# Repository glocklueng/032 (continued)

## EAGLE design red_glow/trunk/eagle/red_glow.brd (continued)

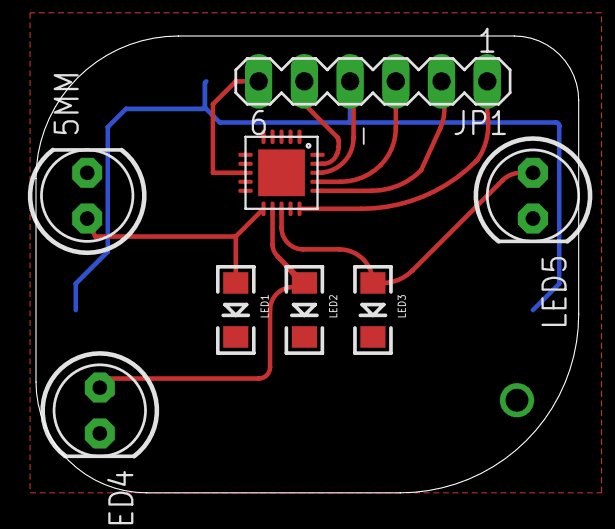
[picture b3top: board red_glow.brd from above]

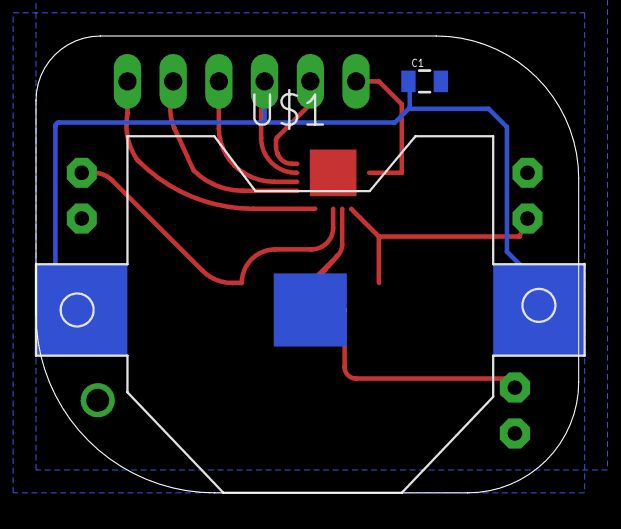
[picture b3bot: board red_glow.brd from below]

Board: 2 copper layers, 30.2 x 25.4 mm, 10 parts (2 on the bottom side), 9 nets.

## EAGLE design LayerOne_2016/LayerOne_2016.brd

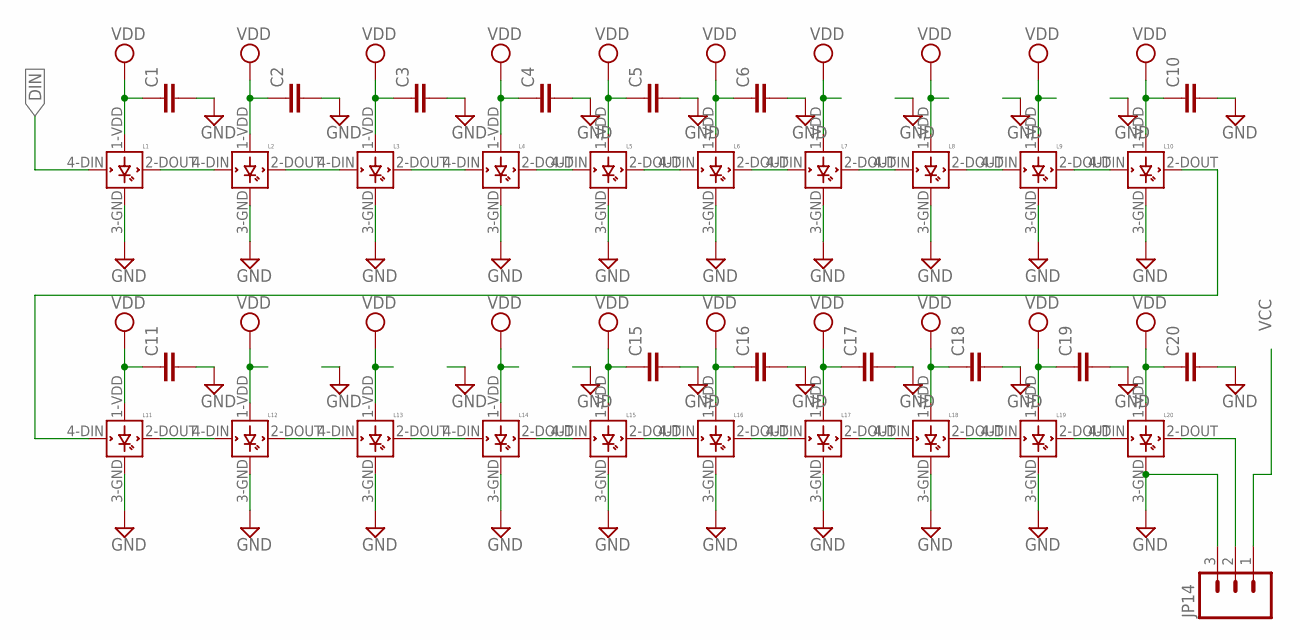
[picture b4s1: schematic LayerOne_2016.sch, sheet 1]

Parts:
C1, C2, C3, C4, C5, C6, C10, C11, C15, C16, C17, C18, C19, C20: CAP0805; 0805
JP14: M031X03_NO_SILK; 1X03_NO_SILK
L1, L2, L3, L4, L5, L6, L7, L8, L9, L10, L11, L12, L13, L14, L15, L16, L17, L18, L19, L20: WS2812B

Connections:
DIN: L1.4-DIN (DIN); also elsewhere on the board
GND: C1.2, C2.2, C3.2, C4.2, C5.2, C6.2, C10.2, C11.2, C15.2, C16.2, C17.2, C18.2, C19.2, C20.2, JP14.3, L1.3-GND (GND), L2.3-GND (GND), L3.3-GND (GND), L4.3-GND (GND), L5.3-GND (GND), L6.3-GND (GND), L7.3-GND (GND), L8.3-GND (GND), L9.3-GND (GND), L10.3-GND (GND), L11.3-GND (GND), L12.3-GND (GND), L13.3-GND (GND), L14.3-GND (GND), L15.3-GND (GND), L16.3-GND (GND), L17.3-GND (GND), L18.3-GND (GND), L19.3-GND (GND), L20.3-GND (GND); also elsewhere on the board
unnamed: L1.2-DOUT (DOUT), L2.4-DIN (DIN)
unnamed: L3.2-DOUT (DOUT), L4.4-DIN (DIN)
unnamed: L4.2-DOUT (DOUT), L5.4-DIN (DIN)
unnamed: L5.2-DOUT (DOUT), L6.4-DIN (DIN)
unnamed: L6.2-DOUT (DOUT), L7.4-DIN (DIN)
unnamed: L7.2-DOUT (DOUT), L8.4-DIN (DIN)
unnamed: L8.2-DOUT (DOUT), L9.4-DIN (DIN)
unnamed: L9.2-DOUT (DOUT), L10.4-DIN (DIN)
unnamed: L11.2-DOUT (DOUT), L12.4-DIN (DIN)
unnamed: L12.2-DOUT (DOUT), L13.4-DIN (DIN)
unnamed: L13.2-DOUT (DOUT), L14.4-DIN (DIN)
unnamed: L14.2-DOUT (DOUT), L15.4-DIN (DIN)
unnamed: L15.2-DOUT (DOUT), L16.4-DIN (DIN)
unnamed: L16.2-DOUT (DOUT), L17.4-DIN (DIN)
unnamed: L17.2-DOUT (DOUT), L18.4-DIN (DIN)
unnamed: L18.2-DOUT (DOUT), L19.4-DIN (DIN)
unnamed: L19.2-DOUT (DOUT), L20.4-DIN (DIN)
unnamed: L10.2-DOUT (DOUT), L11.4-DIN (DIN)
unnamed: JP14.2, L20.2-DOUT (DOUT)
unnamed: L2.2-DOUT (DOUT), L3.4-DIN (DIN)
VCC: C1.1, C2.1, C3.1, C4.1, C5.1, C6.1, C10.1, C11.1, C15.1, C16.1, C17.1, C18.1, C19.1, C20.1, JP14.1, L1.1-VDD (VDD), L2.1-VDD (VDD), L3.1-VDD (VDD), L4.1-VDD (VDD), L5.1-VDD (VDD), L6.1-VDD (VDD), L7.1-VDD (VDD), L8.1-VDD (VDD), L9.1-VDD (VDD), L10.1-VDD (VDD), L11.1-VDD (VDD), L12.1-VDD (VDD), L13.1-VDD (VDD), L14.1-VDD (VDD), L15.1-VDD (VDD), L16.1-VDD (VDD), L17.1-VDD (VDD), L18.1-VDD (VDD), L19.1-VDD (VDD), L20.1-VDD (VDD); also elsewhere on the board

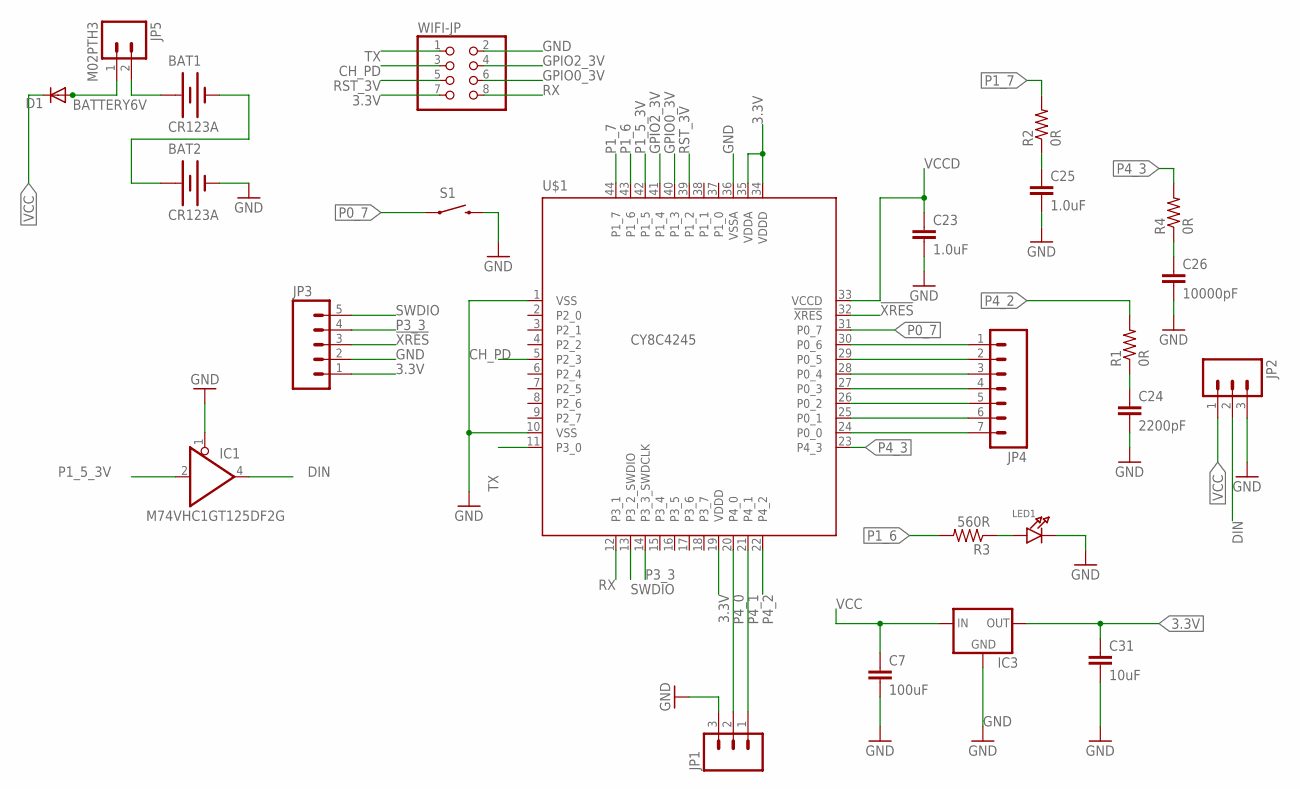
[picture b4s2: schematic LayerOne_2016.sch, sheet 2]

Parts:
BAT1, BAT2: CR123A; TVBGONE-ADJ_BATTERY_CR123A
C7: 100uF; 0805
C23, C25: 1.0uF; 0805
C24: 2200pF; 0805
C26: 10000pF; 0805
C31: 10uF; 0805
D1: DIODESMA; SMA-DIODE
IC1: M74VHC1GT125DF2G; SOT23-5; PARTNO M74VHC1GT125DF2G; DIGIKEY-ND M74VHC1GT125DF1GOSCT-ND
IC3: LM1117; SOT223
JP1, JP2: M031X03_NO_SILK; 1X03_NO_SILK
JP3: M05PTH; 1X05
JP4: M07; 1X07
JP5: M02PTH3; 1X02_LONGPADS
LED1: LED0805; CHIPLED_0805
R1, R2, R4: 0R; 0805
R3: 560R; 0805
S1: SPARKFUN_SWITCH-MOMENTARY-2SMD; SPARKFUN_TACTILE_SWITCH_SMD
U$1: CY8C4245; TQFP44
WIFI-JP: PINHD-2X4; 2X04

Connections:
3.3V: C31.1, IC3.2 (OUT), JP3.1, U$1.19 (VDDD), U$1.34 (VDDD), U$1.35 (VDDA), WIFI-JP.7; also elsewhere on the board
!XRES: JP3.3, U$1.32 (!XRES)
BATTERY6V: D1.A, JP5.1
CH_PD: U$1.5 (P2_3), WIFI-JP.3
DIN: IC1.4 (O), JP2.2; also elsewhere on the board
GND: BAT2.-, C7.2, C23.2, C24.2, C25.2, C26.2, C31.2, IC1.1 (OE), IC1.3 (GND), IC3.1 (GND), JP1.3, JP2.3, JP3.2, LED1.C, S1.3 (2), U$1.1 (VSS), U$1.10 (VSS), U$1.36 (VSSA), WIFI-JP.2; also elsewhere on the board
GPIO0_3V: U$1.40 (P1_3), WIFI-JP.6
GPIO2_3V: U$1.41 (P1_4), WIFI-JP.4
unnamed: C24.1, R1.1
unnamed: C25.1, R2.1
unnamed: C26.1, R4.1
unnamed: LED1.A, R3.1
unnamed: BAT1.-, BAT2.+
unnamed: JP4.7, U$1.24 (P0_0)
unnamed: JP4.6, U$1.25 (P0_1)
unnamed: JP4.5, U$1.26 (P0_2)
unnamed: JP4.4, U$1.27 (P0_3)
unnamed: JP4.3, U$1.28 (P0_4)
unnamed: JP4.2, U$1.29 (P0_5)
unnamed: JP4.1, U$1.30 (P0_6)
unnamed: BAT1.+, JP5.2
P0_7: S1.1, U$1.31 (P0_7)
P1_5_3V: IC1.2 (I), U$1.42 (P1_5)
P1_6: R3.2, U$1.43 (P1_6)
P1_7: R2.2, U$1.44 (P1_7)
P3_3: JP3.4, U$1.14 (P3_3_SWDCLK)
P4_0: JP1.2, U$1.20 (P4_0)
P4_1: JP1.1, U$1.21 (P4_1)
P4_2: R1.2, U$1.22 (P4_2)
P4_3: R4.2, U$1.23 (P4_3)
RST_3V: U$1.39 (P1_2), WIFI-JP.5
RX: U$1.12 (P3_1), WIFI-JP.8
SWDIO: JP3.5, U$1.13 (P3_2_SWDIO)
TX: U$1.11 (P3_0), WIFI-JP.1
VCC: C7.1, D1.C, IC1.5 (VCC), IC3.3 (IN), JP2.1; also elsewhere on the board
VCCD: C23.1, U$1.33 (VCCD)

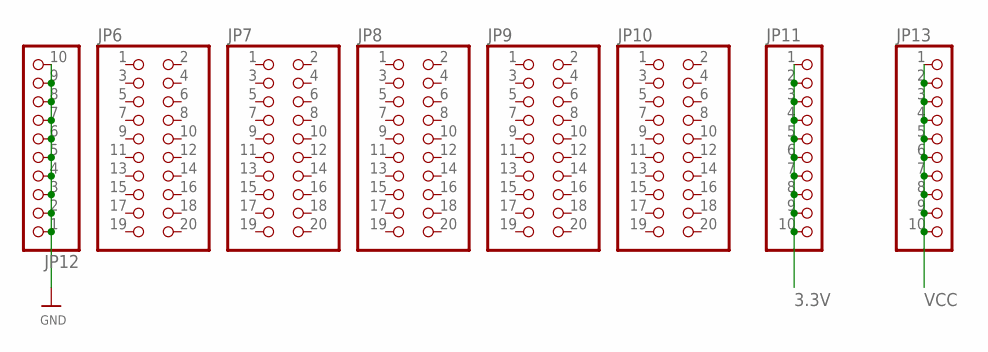
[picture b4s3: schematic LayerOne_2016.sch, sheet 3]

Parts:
JP6, JP7, JP8, JP9, JP10: PINHD-2X10; 2X10
JP11, JP12, JP13: HEADER-1X10; 1X10_OVAL

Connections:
3.3V: JP11.1, JP11.2, JP11.3, JP11.4, JP11.5, JP11.6, JP11.7, JP11.8, JP11.9, JP11.10; also elsewhere on the board
GND: JP12.1, JP12.2, JP12.3, JP12.4, JP12.5, JP12.6, JP12.7, JP12.8, JP12.9, JP12.10; also elsewhere on the board
VCC: JP13.1, JP13.2, JP13.3, JP13.4, JP13.5, JP13.6, JP13.7, JP13.8, JP13.9, JP13.10; also elsewhere on the board

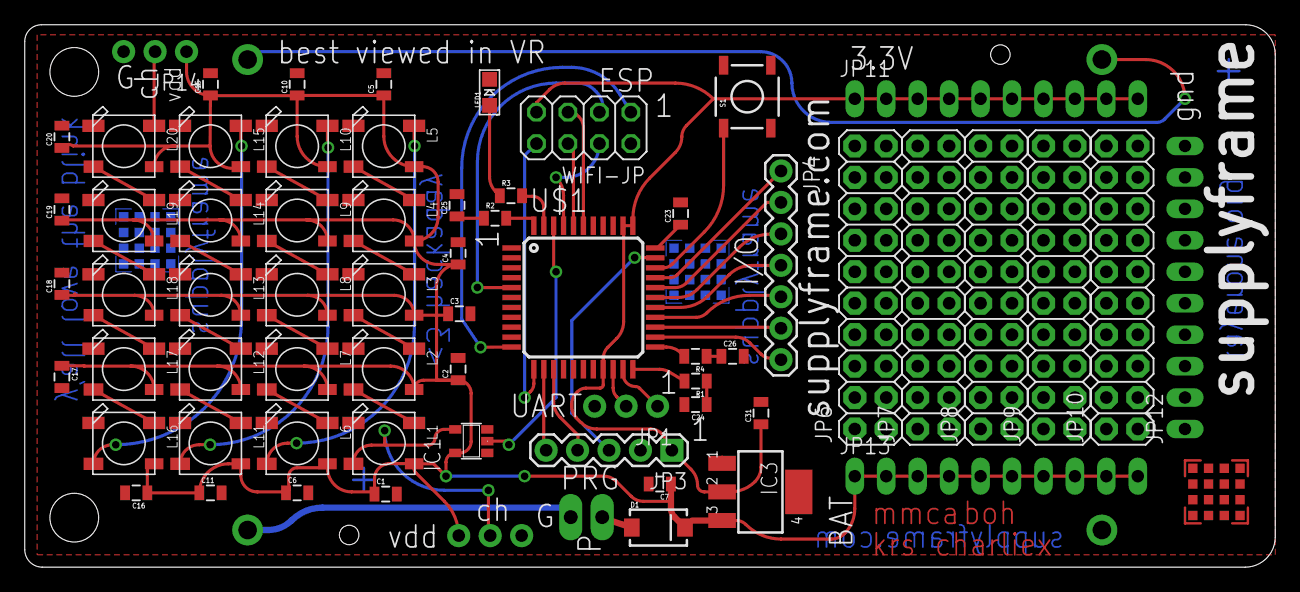
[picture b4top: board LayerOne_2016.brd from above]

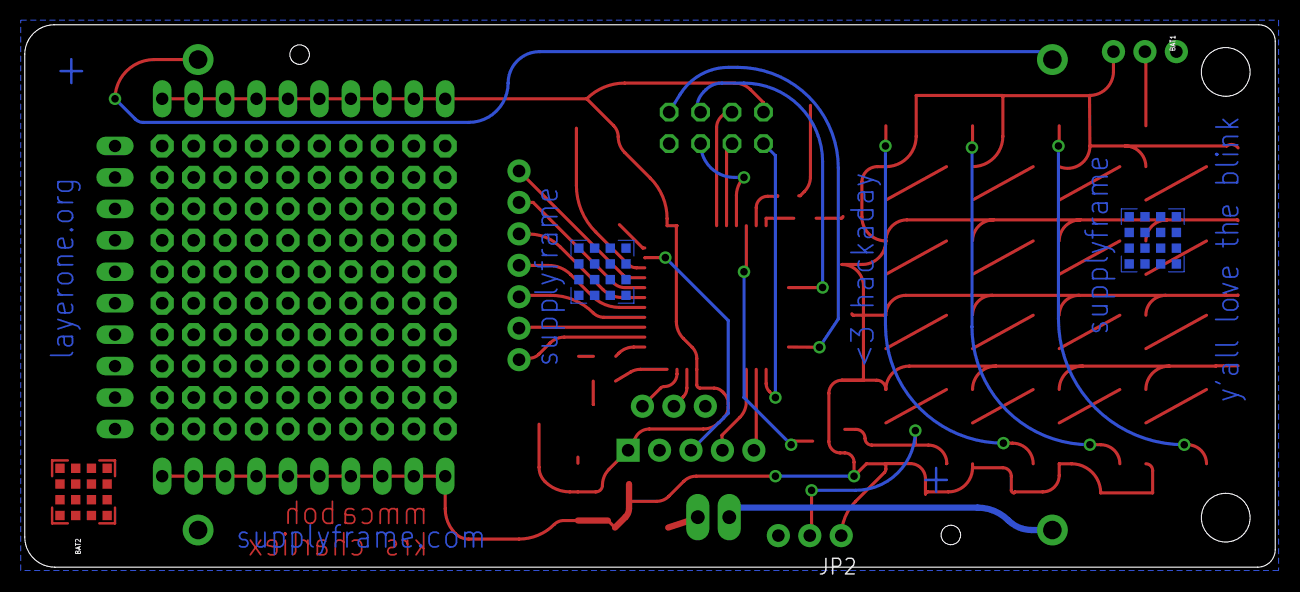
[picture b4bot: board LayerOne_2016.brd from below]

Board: 2 copper layers, 101.0 x 43.8 mm, 67 parts (3 on the bottom side), 56 nets.

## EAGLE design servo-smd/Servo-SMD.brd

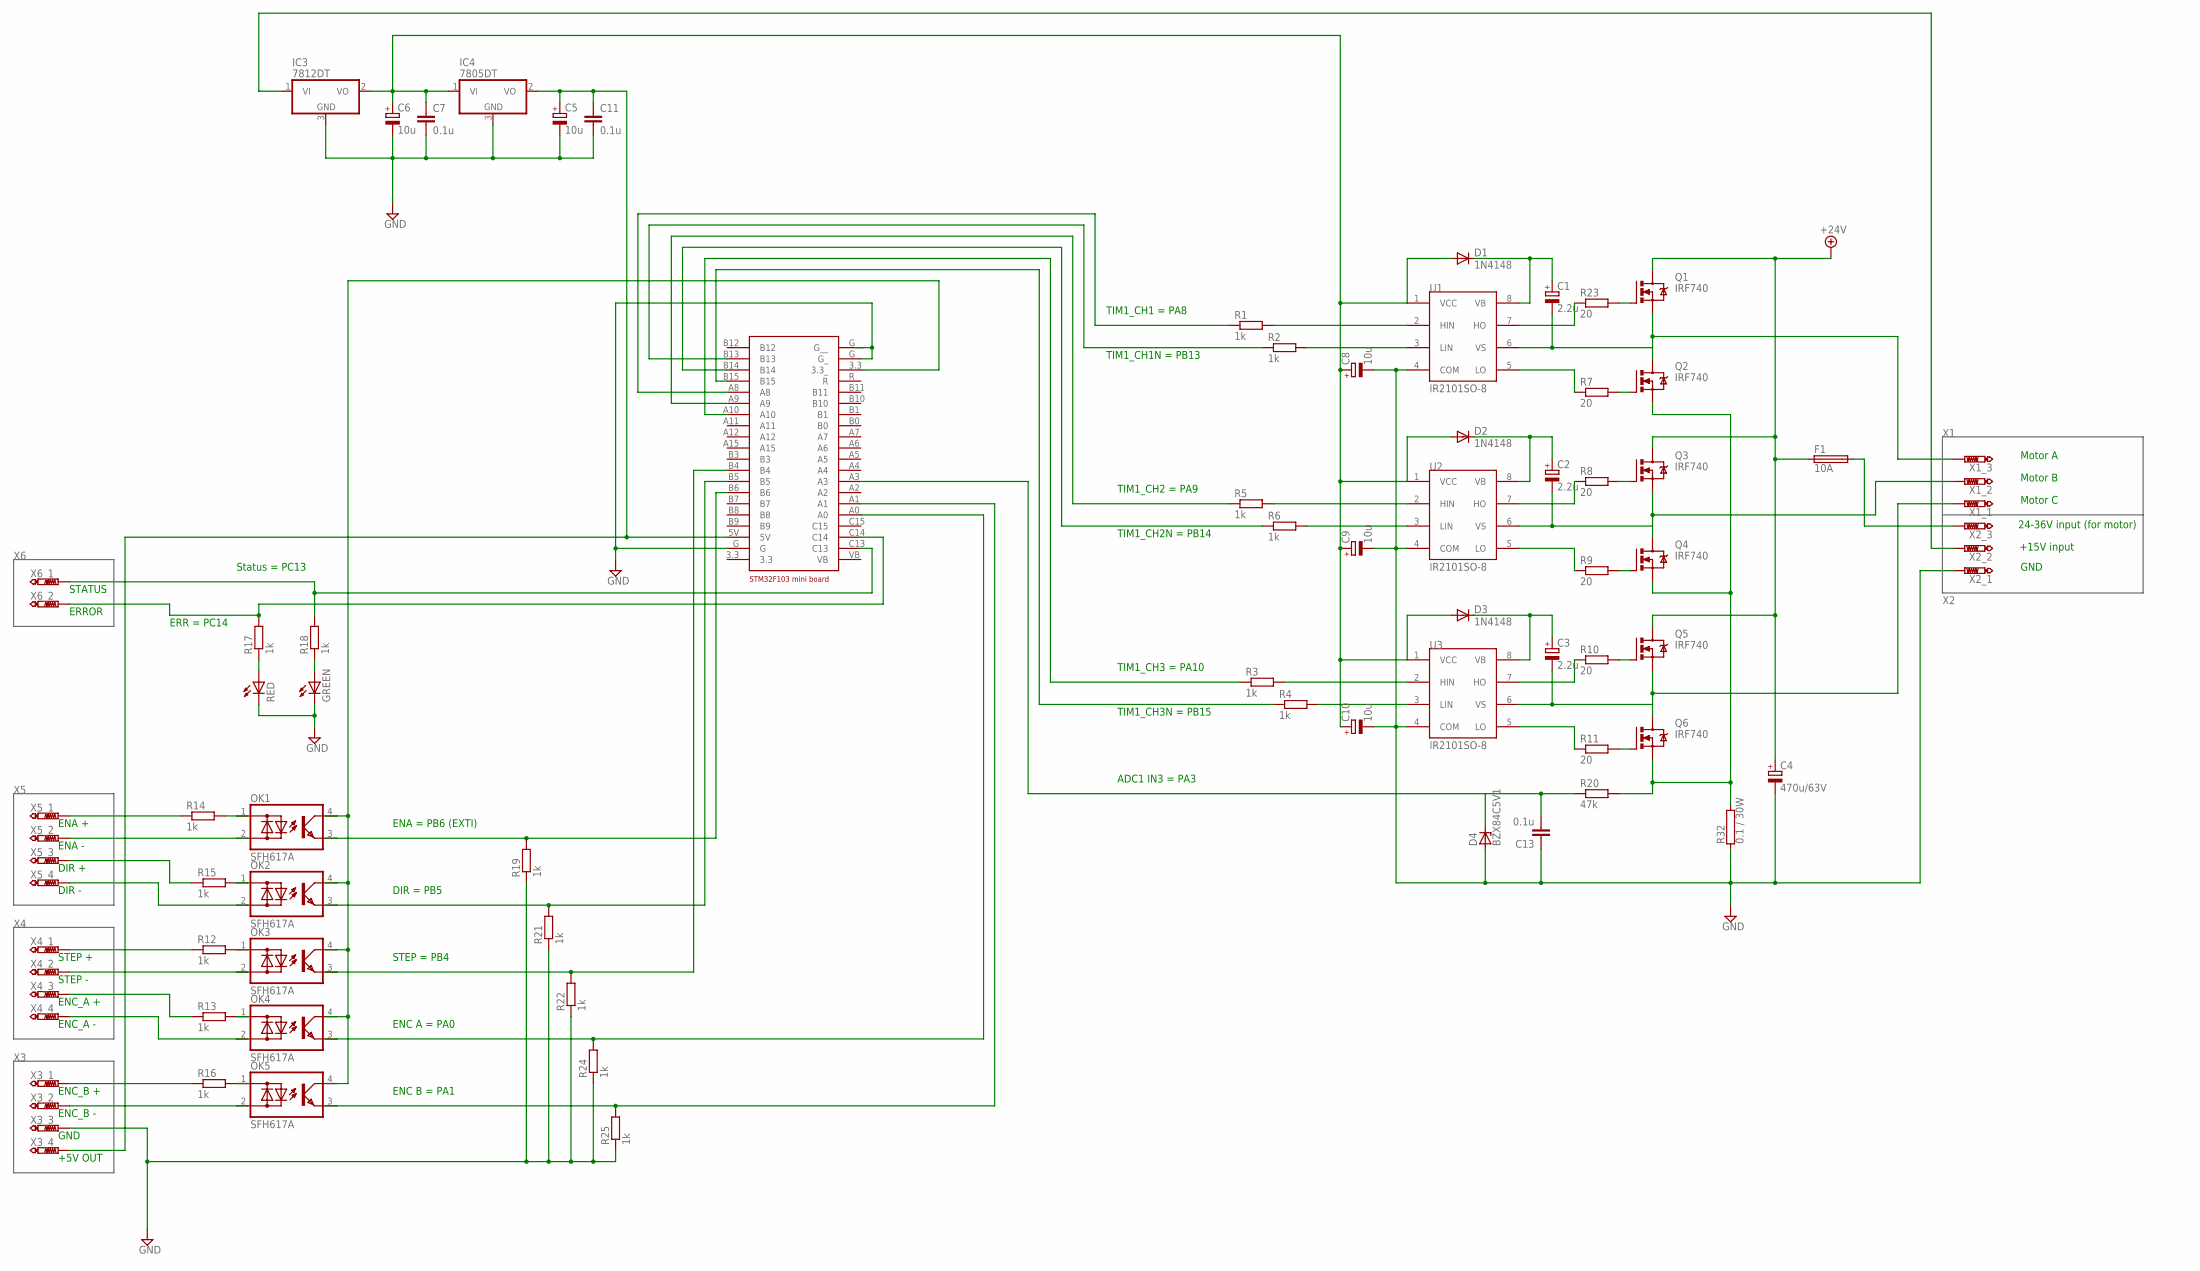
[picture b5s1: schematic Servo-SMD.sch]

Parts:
C1, C2, C3: 2.2u; SANYO-OSCON_SMD_C6
C4: 470u/63V; E5-13
C5, C6, C8, C9, C10: 10u; SANYO-OSCON_SMD_C6
C7, C11, C13: 0.1u; C0805
D1, D2, D3: 1N4148; SOD-123_MINI-SMA
D4: BZX84C5V1; TO236
F1: 10A; SHK20L
GREEN: LEDSML0805; SML0805
IC3: 7812DT; TO252
IC4: 7805DT; TO252
OK1, OK2, OK3, OK4, OK5: SFH617A; DIL4-SMD
Q1, Q2, Q3, Q4, Q5, Q6: IRF740; TO220BV
R1, R2, R3, R4, R5, R6, R12, R13, R14, R15, R16, R17, R18, R19, R21, R22, R24, R25: 1k; M0805
R7, R8, R9, R10, R11, R23: 20; M0805
R20: 47k; M0805
R32: 0.1 / 30W; TO220-2
RED: LEDSML0805; SML0805
U1, U2, U3: IR2101SO-8; SO-8
U$1: STM32F108; STB32F108BRD
X1_1, X1_2, X1_3, X2_1, X2_2, X2_3, X3_1, X3_2, X3_3, X3_4, X4_1, X4_2, X4_3, X4_4, X5_1, X5_2, X5_3, X5_4, X6_1, X6_2: PTR1PAD1-13Y; P1-13Y

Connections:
+12V: IC3.1 (VI), X2_2.TP
+24V: C4.+, F1.1A (1), Q1.D, Q3.D, Q5.D
GND: C4.-, C5.-, C6.-, C7.2, C8.-, C9.-, C10.-, C11.2, C13.1, D4.A, GREEN.C, IC3.3 (GND), IC4.3 (GND), R19.1, R21.1, R22.1, R24.1, R25.1, R32.P$1 (1), RED.C, U1.4 (COM), U2.4 (COM), U3.4 (COM), U$1.G, U$1.G_, U$1.G__, X2_1.TP, X3_3.TP
unnamed: OK3.1 (AC1), R12.2
unnamed: OK4.1 (AC1), R13.2
unnamed: R1.1, U$1.A8
unnamed: R2.1, U$1.B13
unnamed: R5.1, U$1.A9
unnamed: R6.1, U$1.B14
unnamed: R3.1, U$1.A10
unnamed: R4.1, U$1.B15
unnamed: R2.2, U1.3 (LIN)
unnamed: R1.2, U1.2 (HIN)
unnamed: R5.2, U2.2 (HIN)
unnamed: R6.2, U2.3 (LIN)
unnamed: R4.2, U3.3 (LIN)
unnamed: R3.2, U3.2 (HIN)
unnamed: R23.1, U1.7 (HO)
unnamed: OK1.1 (AC1), R14.2
unnamed: R7.1, U1.5 (LO)
unnamed: R9.1, U2.5 (LO)
unnamed: R8.1, U2.7 (HO)
unnamed: R10.1, U3.7 (HO)
unnamed: R11.1, U3.5 (LO)
unnamed: C1.-, Q1.S, Q2.D, U1.6 (VS), X1_3.TP
unnamed: C2.-, Q3.S, Q4.D, U2.6 (VS), X1_2.TP
unnamed: C3.-, Q5.S, Q6.D, U3.6 (VS), X1_1.TP
unnamed: Q1.G, R23.2
unnamed: Q2.G, R7.2
unnamed: Q3.G, R8.2
unnamed: Q4.G, R9.2
unnamed: Q5.G, R10.2
unnamed: Q6.G, R11.2
unnamed: OK2.1 (AC1), R15.2
unnamed: C5.+, C11.1, IC4.2 (VO), U$1.5V, X3_4.TP
unnamed: OK5.1 (AC1), R16.2
unnamed: R12.1, X4_1.TP
unnamed: OK3.2 (AC2), X4_2.TP
unnamed: R13.1, X4_3.TP
unnamed: OK4.2 (AC2), X4_4.TP
unnamed: R14.1, X5_1.TP
unnamed: OK1.2 (AC2), X5_2.TP
unnamed: Q2.S, Q4.S, Q6.S, R20.2, R32.P$2 (2)
unnamed: R15.1, X5_3.TP
unnamed: OK2.2 (AC2), X5_4.TP
unnamed: R16.1, X3_1.TP
unnamed: OK5.2 (AC2), X3_2.TP
unnamed: OK1.4 (C), OK2.4 (C), OK3.4 (C), OK4.4 (C), OK5.4 (C), U$1.3.3_
unnamed: OK5.3 (E), R25.2, U$1.A1
unnamed: OK4.3 (E), R24.2, U$1.A0
unnamed: OK3.3 (E), R22.2, U$1.B4
unnamed: OK2.3 (E), R21.2, U$1.B5
unnamed: OK1.3 (E), R19.2, U$1.B6
unnamed: R17.2, U$1.C14, X6_2.TP
unnamed: R18.2, U$1.C13, X6_1.TP
unnamed: R17.1, RED.A
unnamed: GREEN.A, R18.1
unnamed: F1.2A (2), X2_3.TP
unnamed: C13.2, D4.C, R20.1, U$1.A3
VB1: C1.+, D1.C, U1.8 (VB)
VB2: C2.+, D2.C, U2.8 (VB)
VB3: C3.+, D3.C, U3.8 (VB)
VCC: C6.+, C7.1, C8.+, C9.+, C10.+, D1.A, D2.A, D3.A, IC3.2 (VO), IC4.1 (VI), U1.1 (VCC), U2.1 (VCC), U3.1 (VCC)

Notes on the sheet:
+15V input
24-36V input (for motor)
GND
Motor A
Motor B
Motor C
ENC B = PA1
ENC A = PA0
STEP = PB4
DIR = PB5
ENA = PB6 (EXTI)
TIM1_CH1N = PB13
TIM1_CH1 = PA8
TIM1_CH2N = PB14
TIM1_CH2 = PA9
TIM1_CH3N = PB15
TIM1_CH3 = PA10
ADC1 IN3 = PA3
ERR = PC14
Status = PC13
+5V OUT
ENC_B -
ENC_B +
ENC_A -
ENC_A +
STEP -
STEP +
DIR -
DIR +
ENA -
ENA +
ERROR
STATUS

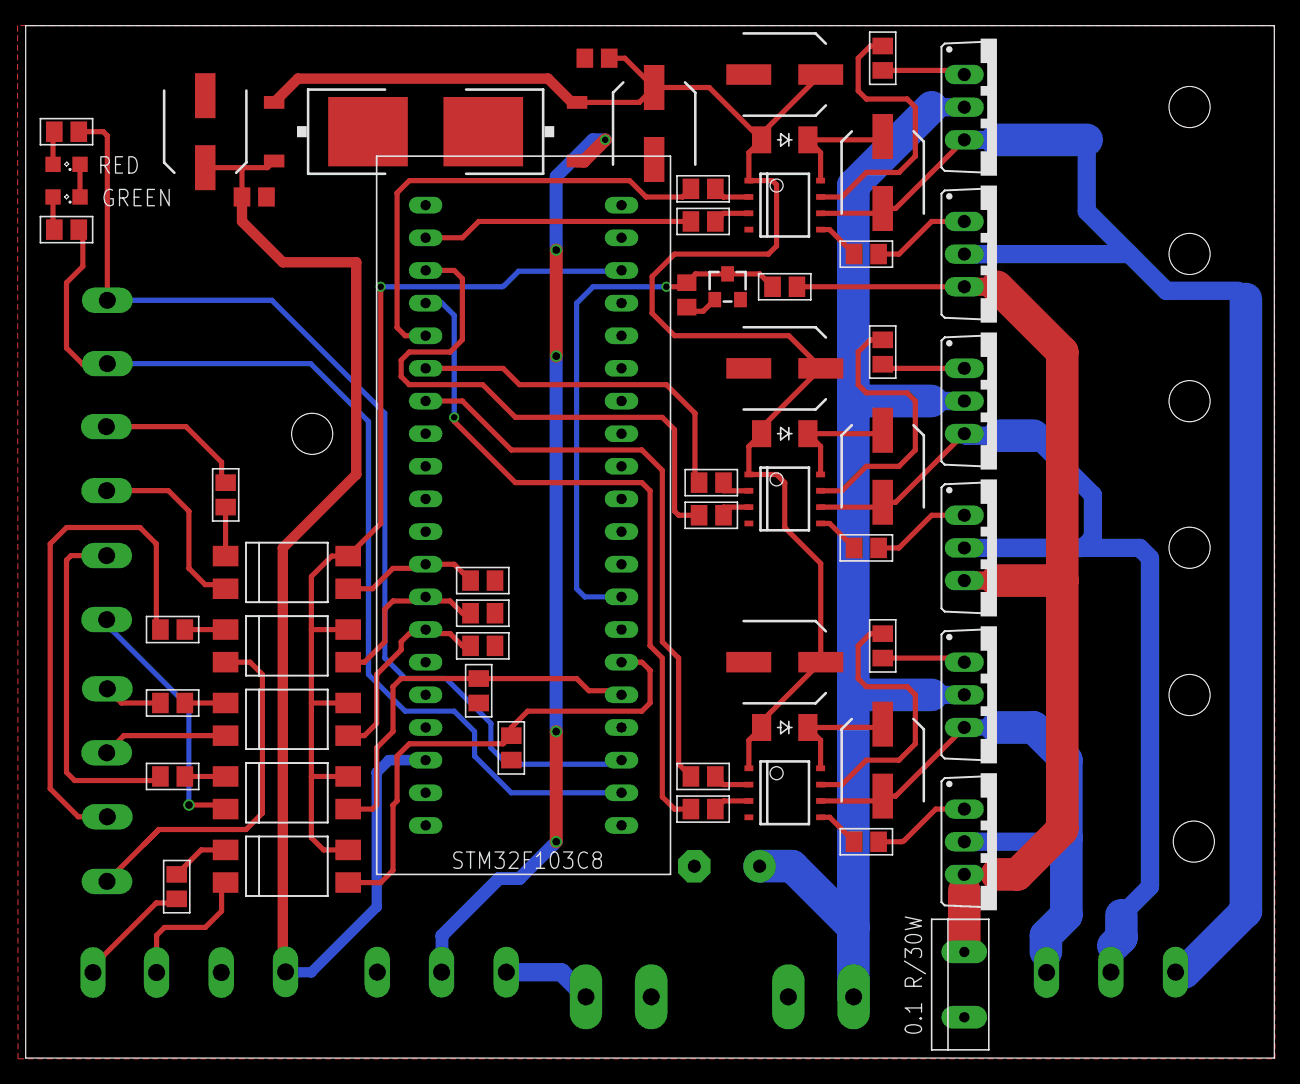
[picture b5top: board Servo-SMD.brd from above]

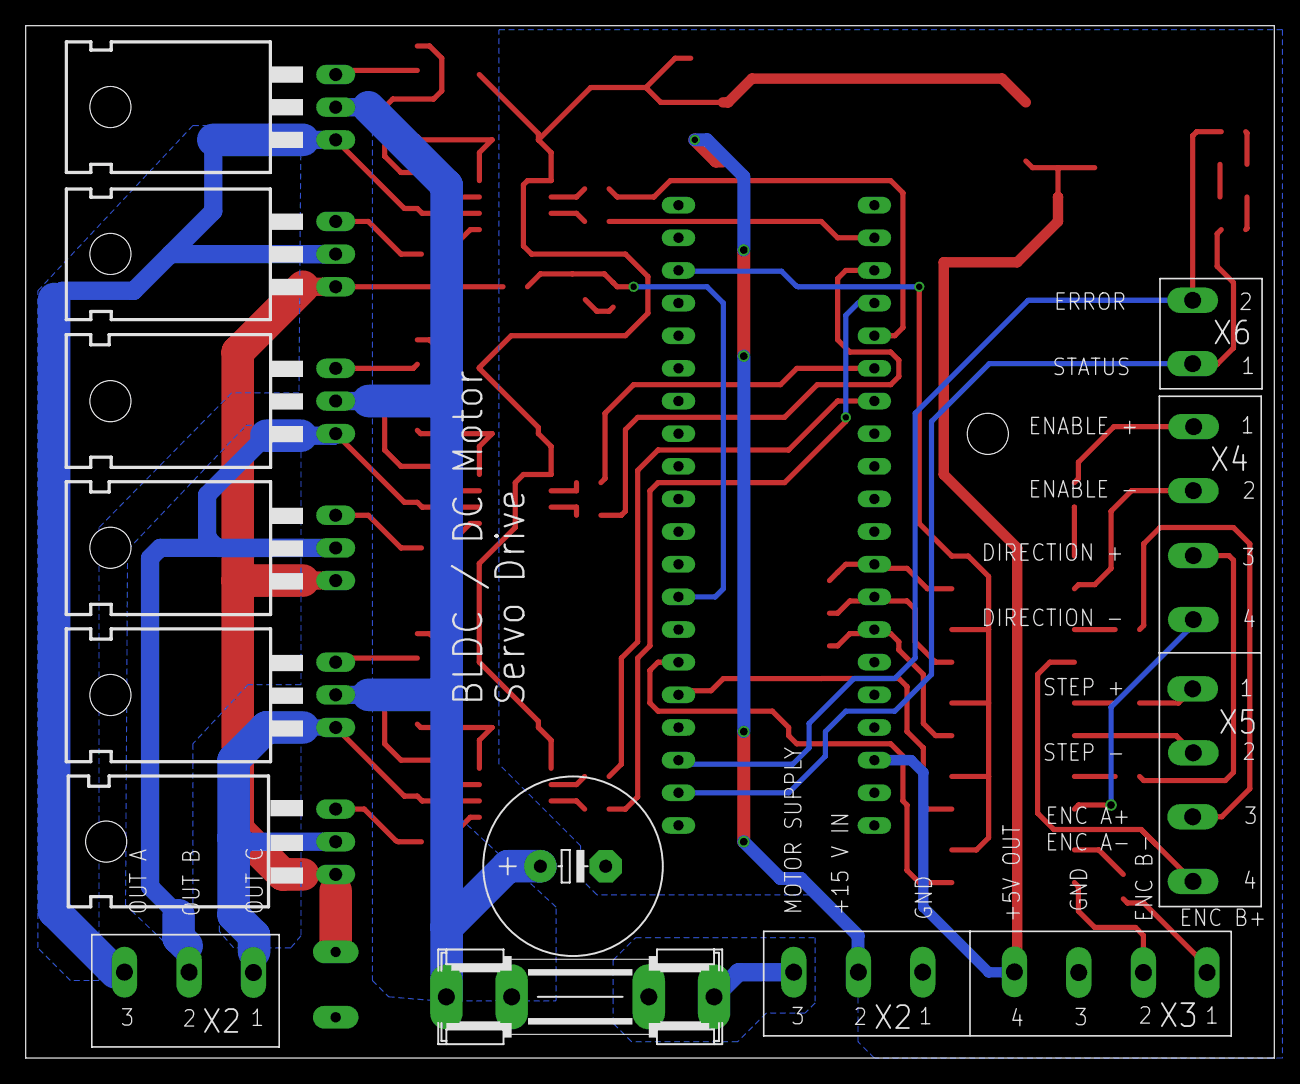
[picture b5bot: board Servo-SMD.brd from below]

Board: 2 copper layers, 97.1 x 80.3 mm, 82 parts (2 on the bottom side), 63 nets.

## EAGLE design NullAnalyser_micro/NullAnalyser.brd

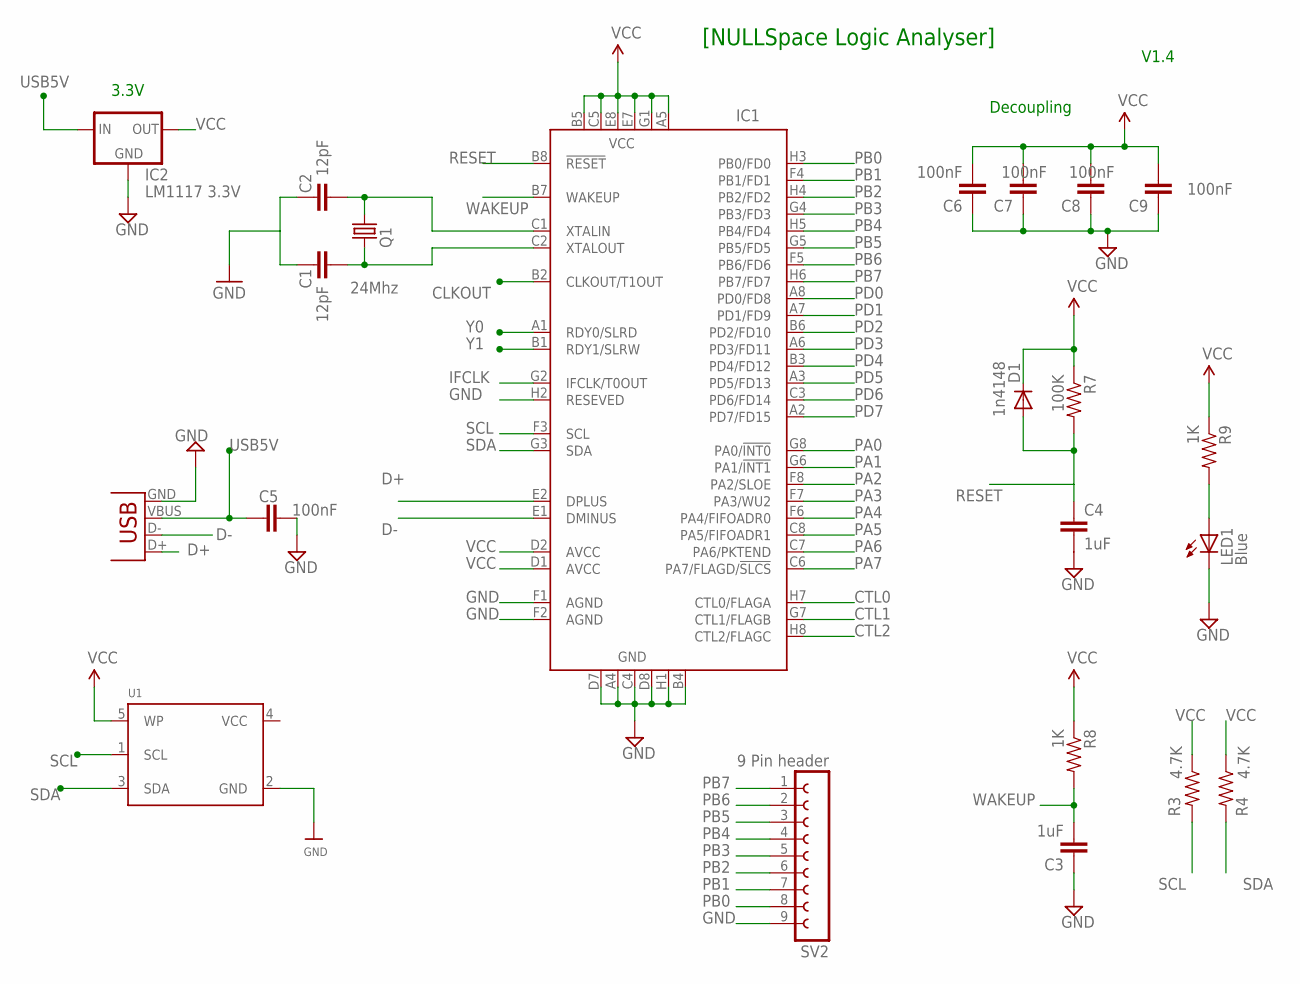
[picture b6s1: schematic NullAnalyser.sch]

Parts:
C1, C2: 12pF; 0402-CAP; MPN C0805C120J5GACTU
C3, C4: 1uF; 0402-CAP; MPN C2012Y5V1C105Z/0.85
C5, C6, C7, C8, C9: 100nF; 0402-CAP; MPN GRM21BR71H104KA01L
D1: 1n4148; SOD-323; MPN 1N4148W-V-GS08
IC1: CY7C68014A-56BAXC; VFBGA56; MPN CY7C68014A-56BAXC
IC2: LM1117 3.3V; SOT223; MPN LM1117MPX-3.3
LED1: Blue; LED-0603; MPN 5988210107F
Q1: 24Mhz; CRYSTAL-SMD-TWO-PAD; MPN ABM3-24.000MHZ-B2-T
R3, R4: 4.7K; 0402-RES; MPN CRCW08054K70JNEA
R7: 100K; 0402-RES; MPN MCTF0805DTC1002
R8, R9: 1K; 0402-RES; MPN MCTF0805DTC1001
SV2: 9 Pin header; FE09
U1: MCP24AA32; SOT23-5; MPN 24LC00T-I/OT
X1: USB-MICROB; MPN 1734035-1

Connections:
CLKOUT: IC1.B2 (CLKOUT/T1OUT)
CTL0: IC1.H7 (CTL0/FLAGA)
CTL1: IC1.G7 (CTL1/FLAGB)
CTL2: IC1.H8 (CTL2/FLAGC)
D+: IC1.E2 (DPLUS), X1.D+
D-: IC1.E1 (DMINUS), X1.D-
GND: C1.1, C2.2, C3.1, C4.2, C5.2, C6.1, C7.1, C8.1, C9.1, IC1.A4 (GND), IC1.B4 (GND), IC1.C4 (GND), IC1.D7 (GND), IC1.D8 (GND), IC1.F1 (AGND), IC1.F2 (AGND), IC1.H1 (GND), IC1.H2 (RESEVED), IC2.1 (GND), LED1.C, SV2.9, U1.2 (GND), X1.GND
IFCLK: IC1.G2 (IFCLK/T0OUT)
unnamed: LED1.A, R9.2
unnamed: C2.1, IC1.C1 (XTALIN), Q1.2
unnamed: C1.2, IC1.C2 (XTALOUT), Q1.1
PA0: IC1.G8 (PA0/!INT0)
PA1: IC1.G6 (PA1/!INT1)
PA2: IC1.F8 (PA2/SLOE)
PA3: IC1.F7 (PA3/WU2)
PA4: IC1.F6 (PA4/FIFOADR0)
PA5: IC1.C8 (PA5/FIFOADR1)
PA6: IC1.C7 (PA6/PKTEND)
PA7: IC1.C6 (PA7/FLAGD/!SLCS)
PB0: IC1.H3 (PB0/FD0), SV2.8
PB1: IC1.F4 (PB1/FD1), SV2.7
PB2: IC1.H4 (PB2/FD2), SV2.6
PB3: IC1.G4 (PB3/FD3), SV2.5
PB4: IC1.H5 (PB4/FD4), SV2.4
PB5: IC1.G5 (PB5/FD5), SV2.3
PB6: IC1.F5 (PB6/FD6), SV2.2
PB7: IC1.H6 (PB7/FD7), SV2.1
PD0: IC1.A8 (PD0/FD8)
PD1: IC1.A7 (PD1/FD9)
PD2: IC1.B6 (PD2/FD10)
PD3: IC1.A6 (PD3/FD11)
PD4: IC1.B3 (PD4/FD12)
PD5: IC1.A3 (PD5/FD13)
PD6: IC1.C3 (PD6/FD14)
PD7: IC1.A2 (PD7/FD15)
RESET: C4.1, D1.2 (A), IC1.B8 (!RESET), R7.2
SCL: IC1.F3 (SCL), R3.2, U1.1 (SCL)
SDA: IC1.G3 (SDA), R4.2, U1.3 (SDA)
USB5V: C5.1, IC2.3 (IN), X1.VBUS
VCC: C6.2, C7.2, C8.2, C9.2, D1.1 (C), IC1.A5 (VCC), IC1.B5 (VCC), IC1.C5 (VCC), IC1.D1 (AVCC), IC1.D2 (AVCC), IC1.E7 (VCC), IC1.E8 (VCC), IC1.G1 (VCC), IC2.2 (OUT), R3.1, R4.1, R7.1, R8.1, R9.1, U1.5 (WP)
WAKEUP: C3.2, IC1.B7 (WAKEUP), R8.2
Y0: IC1.A1 (RDY0/SLRD)
Y1: IC1.B1 (RDY1/SLRW)

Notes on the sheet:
[NULLSpace Logic Analyser]
3.3V
V1.4
Decoupling

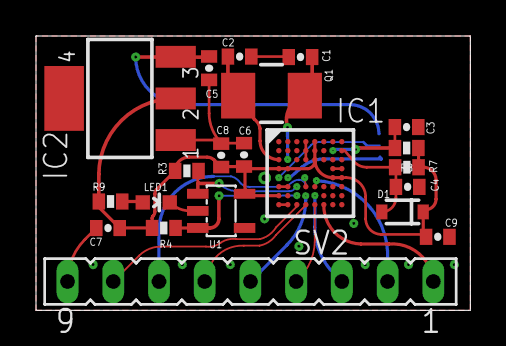
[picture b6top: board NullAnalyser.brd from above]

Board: 2 copper layers, 24.1 x 15.2 mm, 22 parts (1 on the bottom side), 20 nets.

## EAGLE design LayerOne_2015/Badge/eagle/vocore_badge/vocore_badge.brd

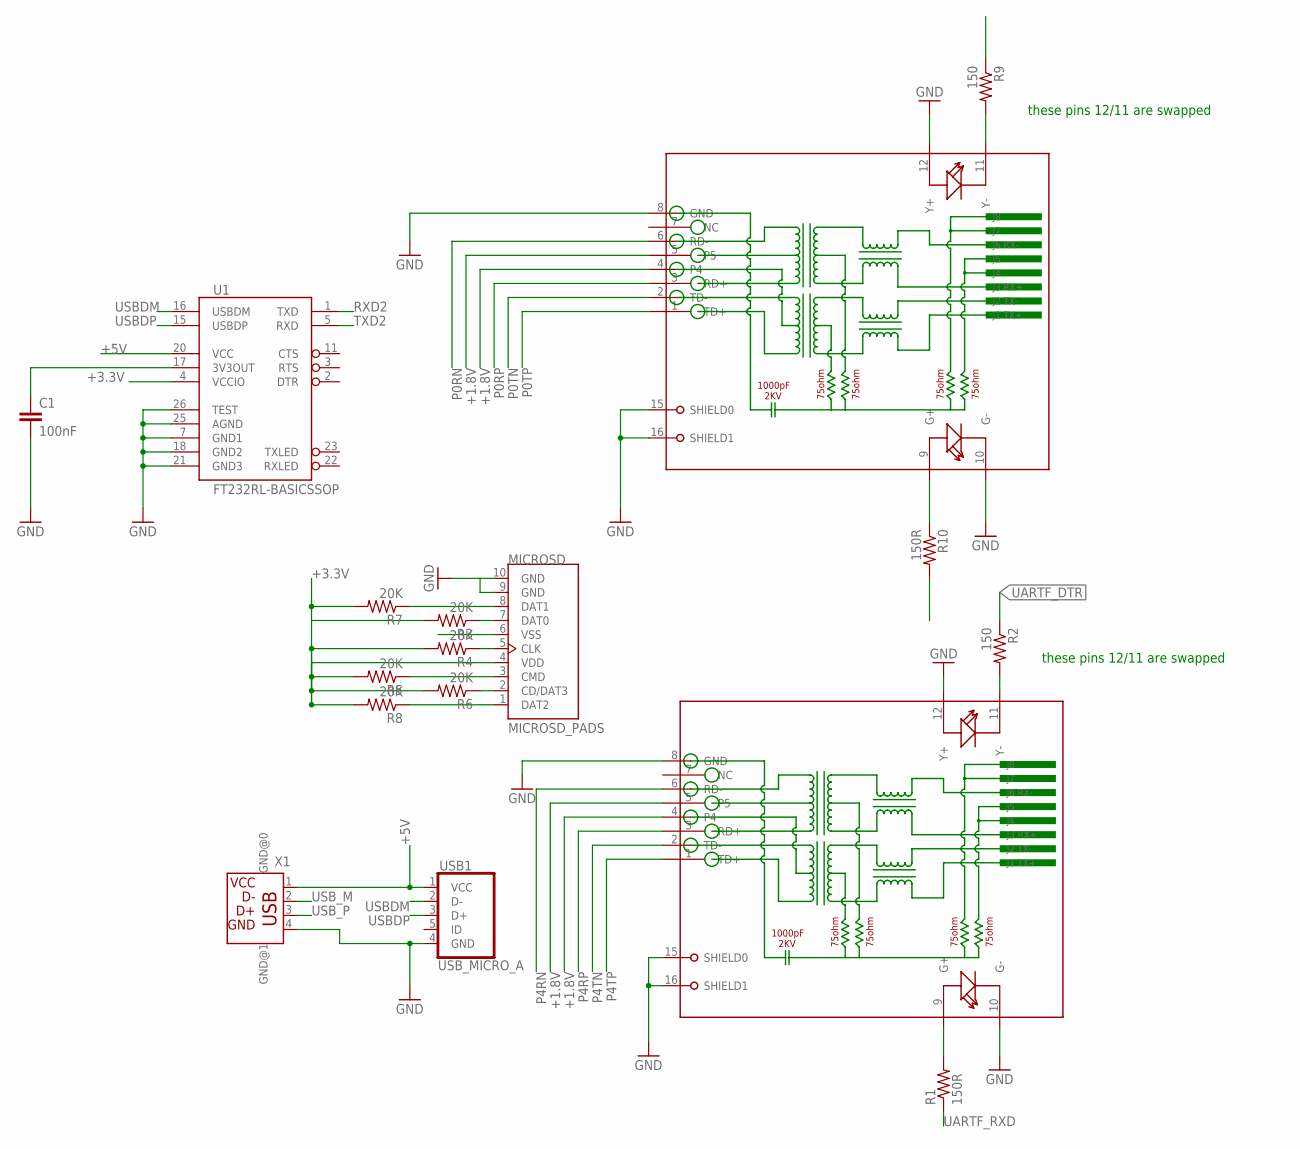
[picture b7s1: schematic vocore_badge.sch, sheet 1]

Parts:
C1: 100nF; 0805
MICROSD: MICROSD_PADS; MICROSD_PADS_1PRIMARY
R1, R10: 150R; 0805
R2, R9: 150; 0805
R3, R4, R5, R6, R7, R8: 20K; 0805
RJ1, RJ45: RJ45ALED; RJ45ALED_1PRIMARY
U1: FT232RL-BASICSSOP; SSOP28DB
USB1: USB_MICRO_A; USB_MICRO_A_1PRIMARY
X1: USB-787616; USB

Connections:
5: X1.GND@0 (5)
6: X1.GND@1 (6)
+1.8V: RJ1.4, RJ1.5, RJ45.4, RJ45.5; also elsewhere on the board
+3.3V: MICROSD.4 (VDD), R3.2, R4.2, R5.2, R6.2, R7.2, R8.2, U1.4 (VCCIO); also elsewhere on the board
+5V: U1.20 (VCC), USB1.1 (VCC), X1.1; also elsewhere on the board
GND: C1.2, MICROSD.6 (VSS), MICROSD.9 (GND), MICROSD.10 (GND), RJ1.8 (GND), RJ1.10 (G-), RJ1.12 (Y+), RJ1.15 (SHIELD0), RJ1.16 (SHIELD1), RJ45.8 (GND), RJ45.10 (G-), RJ45.12 (Y+), RJ45.15 (SHIELD0), RJ45.16 (SHIELD1), U1.7 (GND1), U1.18 (GND2), U1.21 (GND3), U1.25 (AGND), U1.26 (TEST), USB1.4 (GND), X1.4; also elsewhere on the board
LED2: R10.2; also elsewhere on the board
LED3: R9.1; also elsewhere on the board
LED_G: R1.2, RJ45.9 (G+)
LED_Y: R2.2, RJ45.11 (Y-)
unnamed: R9.2, RJ1.11 (Y-)
unnamed: C1.1, U1.17 (3V3OUT)
unnamed: R10.1, RJ1.9 (G+)
P0RN: RJ1.6 (RD-); also elsewhere on the board
P0RP: RJ1.3 (RD+); also elsewhere on the board
P0TN: RJ1.2 (TD-); also elsewhere on the board
P0TP: RJ1.1 (TD+); also elsewhere on the board
P4RN: RJ45.6 (RD-); also elsewhere on the board
P4RP: RJ45.3 (RD+); also elsewhere on the board
P4TN: RJ45.2 (TD-); also elsewhere on the board
P4TP: RJ45.1 (TD+); also elsewhere on the board
RXD2: U1.1 (TXD); also elsewhere on the board
SPI_CLK: MICROSD.5 (CLK), R4.1; also elsewhere on the board
SPI_CS1: MICROSD.2 (CD/DAT3), R6.1; also elsewhere on the board
SPI_MISO: MICROSD.7 (DAT0), R3.1; also elsewhere on the board
SPI_MOSI: MICROSD.3 (CMD), R5.1; also elsewhere on the board
SPI_RSV1: MICROSD.8 (DAT1), R7.1
SPI_RSV2: MICROSD.1 (DAT2), R8.1
TXD2: U1.5 (RXD); also elsewhere on the board
UARTF_DTR: R2.1; also elsewhere on the board
UARTF_RXD: R1.1; also elsewhere on the board
USBDM: U1.16 (USBDM), USB1.2 (D-)
USBDP: U1.15 (USBDP), USB1.3 (D+)
USB_M: X1.2; also elsewhere on the board
USB_P: X1.3; also elsewhere on the board

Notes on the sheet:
these pins 12/11 are swapped
